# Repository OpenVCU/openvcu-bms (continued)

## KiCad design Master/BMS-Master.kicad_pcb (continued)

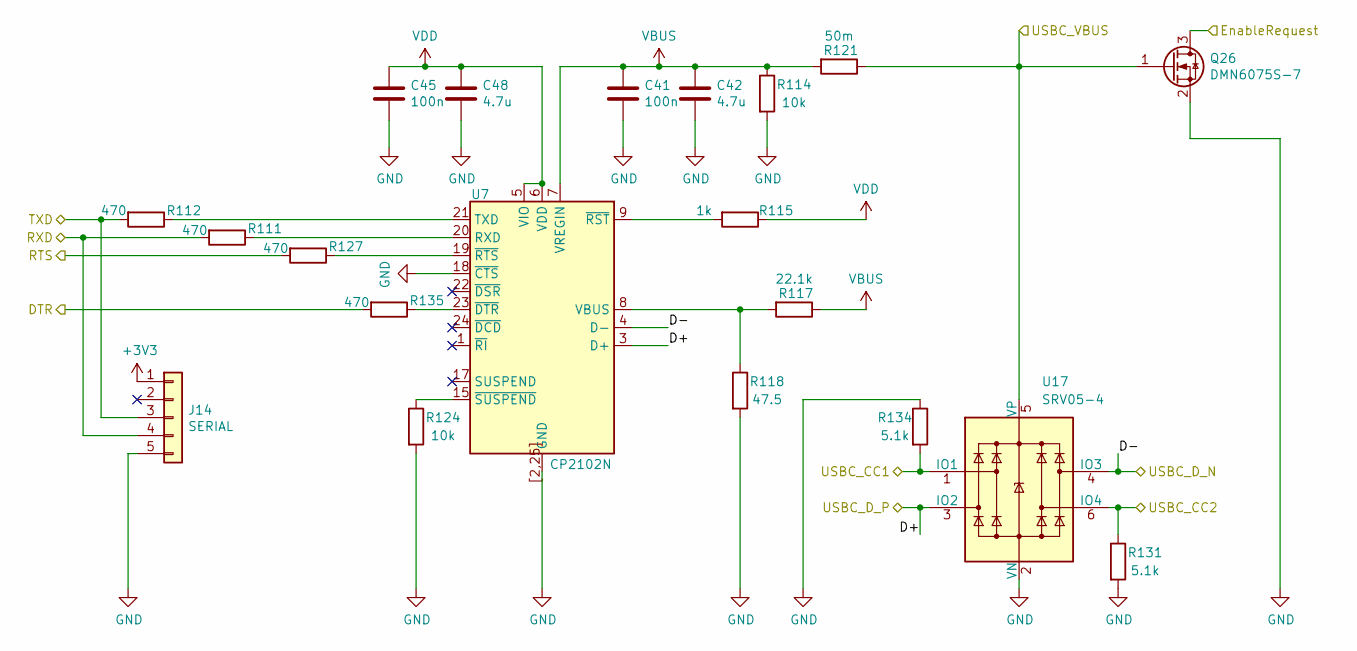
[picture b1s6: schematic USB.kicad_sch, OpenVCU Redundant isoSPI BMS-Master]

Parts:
C41, C45: 100n; C_0603_1608Metric; MPN GRM188R71E104KA01D
C42, C48: 4.7u; C_0805_2012Metric; MPN GRM21BR71E475KA73L
J14: SERIAL; Molex_KK-254_AE-6410-05A_1x05_P2.54mm_Vertical; MPN 70543-0004
Q26: DMN6075S-7; SOT-23; MPN DMN6075S-7
R111, R112, R127, R135: 470; R_0603_1608Metric; MPN RC0603FR-07470RL
R114, R124: 10k; R_0603_1608Metric; MPN RC0603FR-0710KL
R115: 1k; R_0603_1608Metric; MPN MCR03EZPFX1001
R117: 22.1k; R_0603_1608Metric; MPN RC0603FR-0720KL
R118: 47.5; R_0603_1608Metric; MPN RC0603FR-0739KL
R121: 50m; R_1210_3225Metric; MPN RL1210FR-070R05L
R131, R134: 5.1k; R_0603_1608Metric; MPN RC0603FR-075K1L
U7: CP2102N; WQFN-24-1EP_4x4mm_P0.5mm_EP2.45x2.45mm; MPN CP2102N-A02-GQFN24
U17: SRV05-4; SOT-23-6; MPN SRV05-4HTG

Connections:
+3V3: J14.1; also elsewhere on the board
/CAN/EnableRequest: Q26.3 (D); also elsewhere on the board
/LTC6820 STM32/USB_DTR: R135.2; also elsewhere on the board
/LTC6820 STM32/USB_RTS: R127.2; also elsewhere on the board
/LTC6820 STM32/USB_RX: J14.3, R112.2; also elsewhere on the board
/LTC6820 STM32/USB_TX: J14.4, R111.2; also elsewhere on the board
/USB/D+: U7.3 (D+), U17.3 (IO2); also elsewhere on the board
/USB/D-: U7.4 (D-), U17.4 (IO3); also elsewhere on the board
/USB/USBC_CC1: R134.2, U17.1 (IO1); also elsewhere on the board
/USB/USBC_CC2: R131.1, U17.6 (IO4); also elsewhere on the board
/USB/USBC_VBUS: Q26.1 (G), R121.1, U17.5 (VP); also elsewhere on the board
GND: C41.2, C42.2, C45.2, C48.2, J14.5, Q26.2 (S), R114.2, R118.2, R124.2, R131.2, R134.1, U7.2 (GND), U7.18 (~CTS), U7.25 (GND), U7.[2,25] (GND), U17.2 (VN); also elsewhere on the board
unnamed: R111.1, U7.20 (RXD)
unnamed: R112.1, U7.21 (TXD)
unnamed: R117.2, R118.1, U7.8 (VBUS)
unnamed: R135.1, U7.23 (~DTR)
unnamed: R115.2, U7.9 (~RST)
unnamed: R127.1, U7.19 (~RTS)
unnamed: R124.1, U7.15 (~SUSPEND)
VBUS: C41.1, C42.1, R114.1, R117.1, R121.2, U7.7 (VREGIN)
VDD: C45.1, C48.1, R115.1, U7.5 (VIO), U7.6 (VDD)

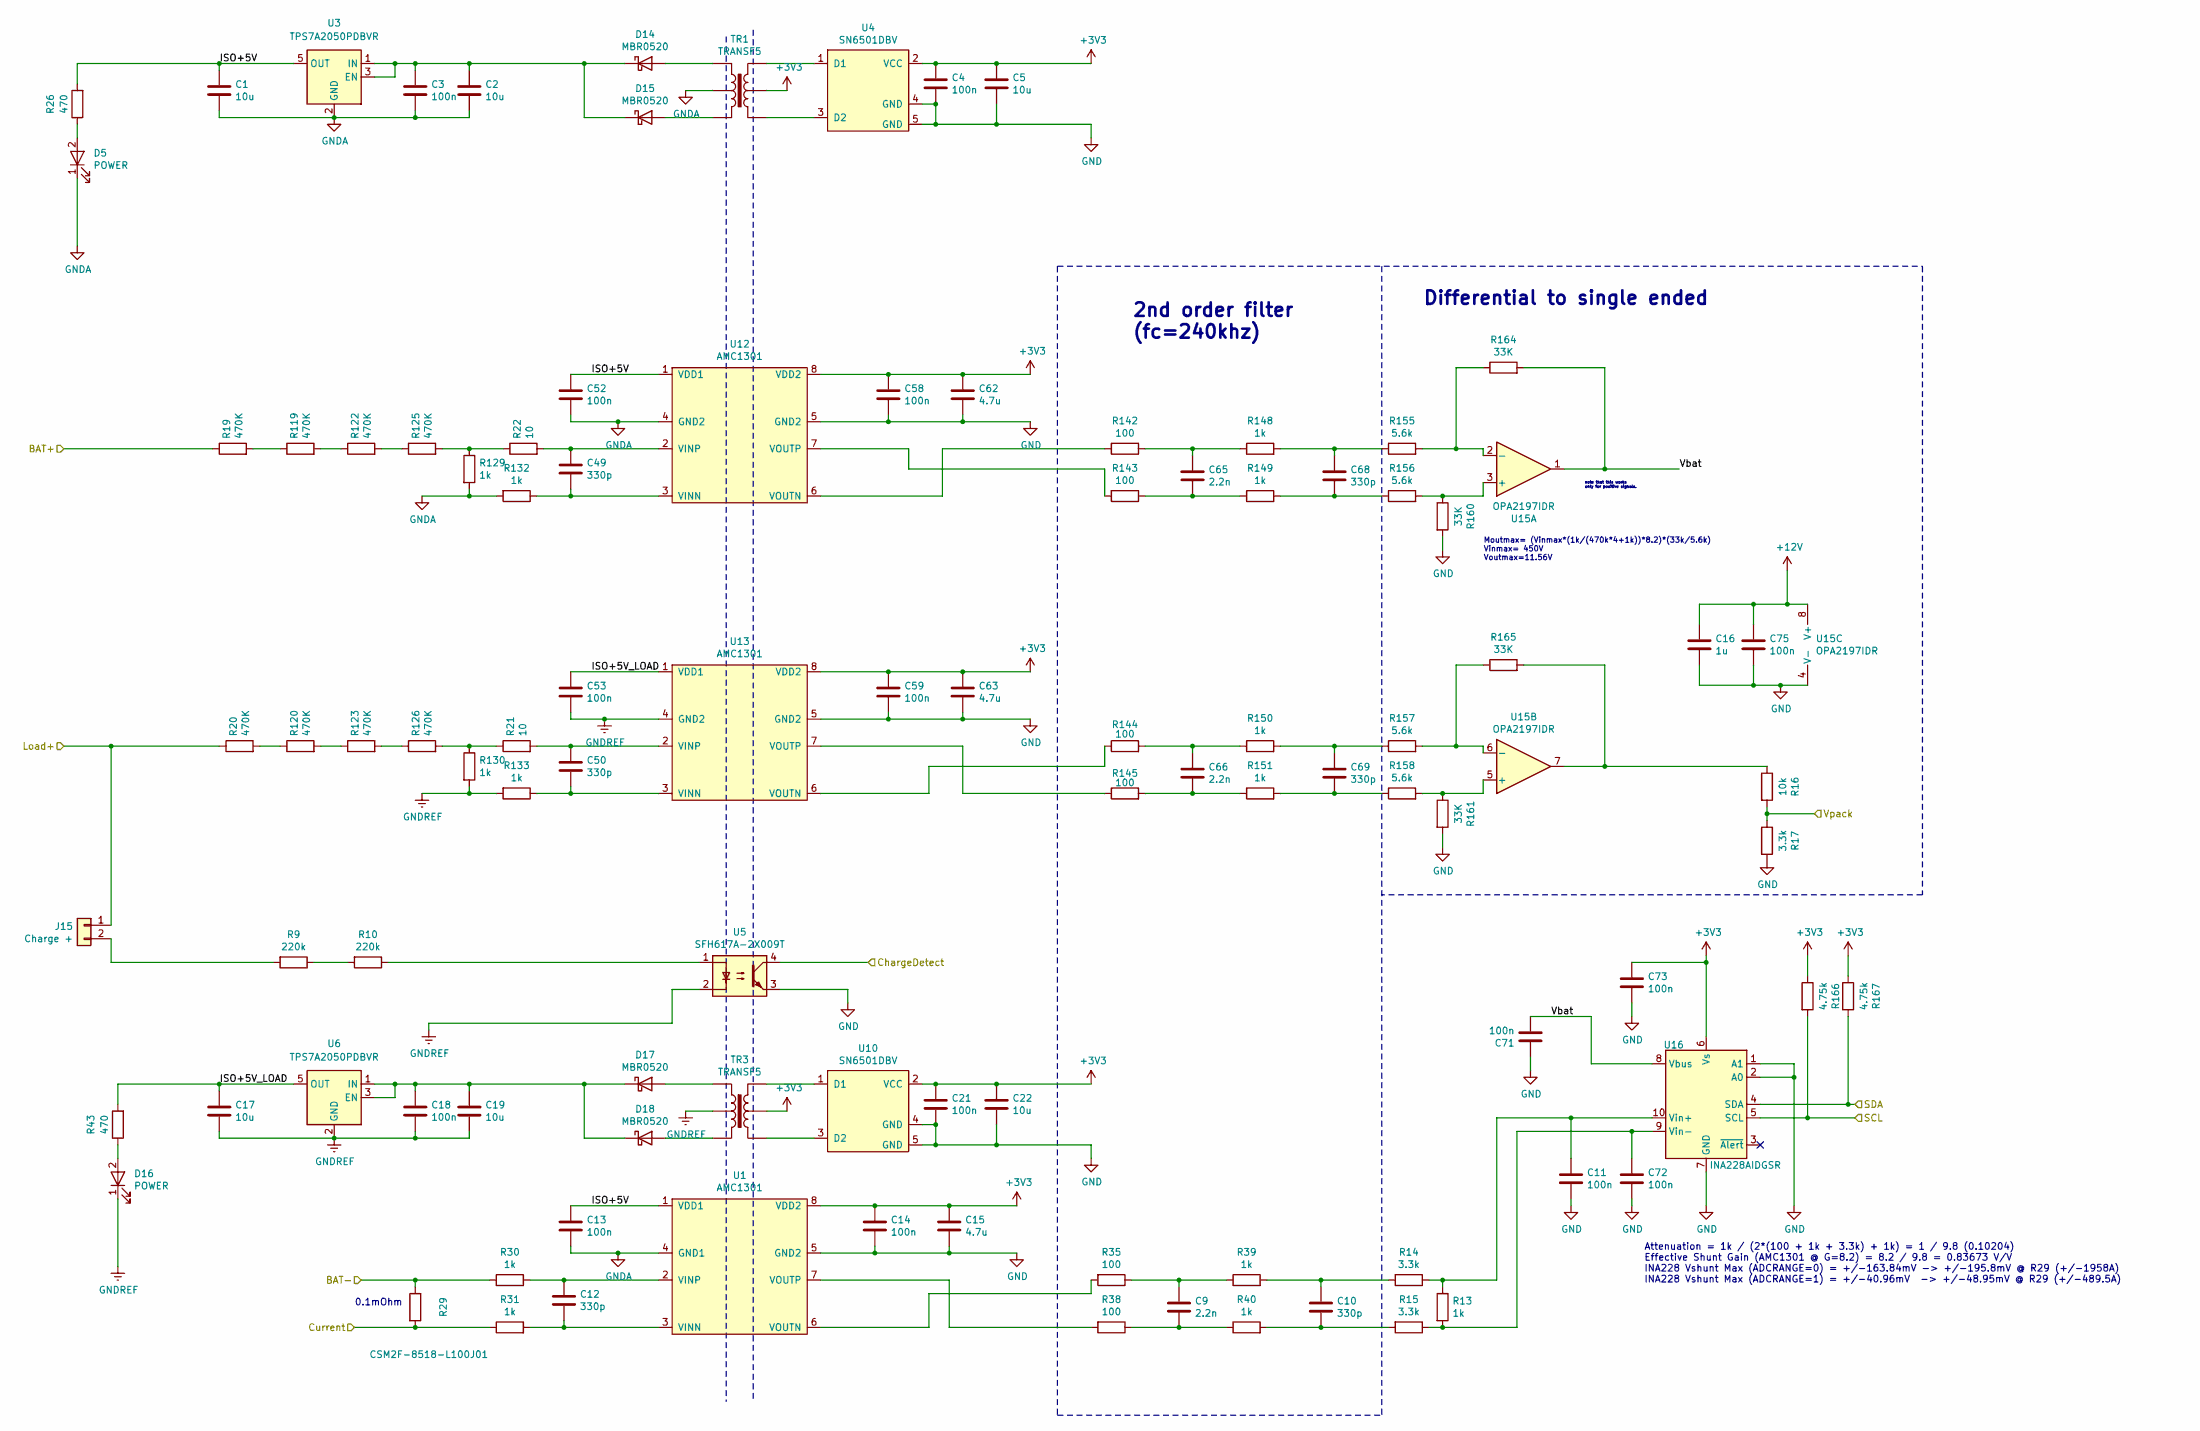
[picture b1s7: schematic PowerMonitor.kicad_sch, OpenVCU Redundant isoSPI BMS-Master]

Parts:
C1, C2, C5, C17, C19, C22: 10u; C_0805_2012Metric; MPN CL21A106KAYNNNE
C3, C4, C11, C13, C14, C18, C21, C52, C53, C58, C59, C71, C72, C73, C75: 100n; C_0603_1608Metric; MPN GRM188R71E104KA01D
C9, C65, C66: 2.2n; C_0603_1608Metric; MPN GRM1885C1H222JA01D
C10, C12, C49, C50, C68, C69: 330p; C_0603_1608Metric; MPN CL10B331KB8NNNC
C15, C62, C63: 4.7u; C_0805_2012Metric; MPN GRM21BR71E475KA73L
C16: 1u; C_0603_1608Metric; MPN GRM188R71E105KA12D
D5, D16: POWER; LED_0603_1608Metric; MPN SML-D12P8WT86C
D14, D15, D17, D18: MBR0520; D_SOD-123; MPN MBR0520L
J15: Charge +; PhoenixContact_GMSTBVA_2,5_2-G_1x02_P7.50mm_Vertical; MPN 1766770
R9, R10: 220k; R_2512_6332Metric; MPN 25121WF2203T4E
R13, R30, R31, R39, R40, R129, R130, R132, R133, R148, R149, R150, R151: 1k; R_0603_1608Metric; MPN MCR03EZPFX1001
R14, R15, R17: 3.3k; R_0603_1608Metric; MPN RC0603FR-073K3L
R16: 10k; R_0603_1608Metric; MPN RC0603FR-0710KL
R19, R20, R119, R120, R122, R123, R125, R126: 470K; R_1206_3216Metric; MPN RC1206FR-07470KL
R21, R22: 10; R_0603_1608Metric; MPN RC0603JR-0710RL
R26, R43: 470; R_0603_1608Metric; MPN RC0603FR-07470RL
R29: CSM2F-8518-L100J01; MPN CSM2F-8518-L100J01
R35, R38, R142, R143, R144, R145: 100; R_0603_1608Metric; MPN RC0603FR-07100RL
R155, R156, R157, R158: 5.6k; R_0603_1608Metric; MPN RC0603FR-075K6L
R160, R161, R164, R165: 33K; R_0603_1608Metric; MPN RC0603FR-0733KL
R166, R167: 4.75k; R_0603_1608Metric; MPN RC0603FR-074K75L
TR1, TR3: TRANSF5; WURTH-760390015; MPN 760390015
U1, U12, U13: AMC1301; SSO-8_6.8x5.9mm_P1.27mm_Clearance8mm; MPN AMC1301DWVR
U3, U6: TPS7A2050PDBVR; SOT-23-5; MPN TPS7A2050PDBVR
U4, U10: SN6501DBV; SOT-23-5; MPN SN6501DBVR
U5: SFH617A-2X009T; SMDIP-4_W9.53mm_Clearance8mm; MPN SFH617A-2X009T
U15: OPA2197IDR; SOIC-8_3.9x4.9mm_P1.27mm; MPN OPA2197IDR
U16: INA228AIDGSR; MSOP-10_3x3mm_P0.5mm; MPN INA228AIDGSR

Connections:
+3V3: C4.1, C5.1, C14.1, C15.1, C21.1, C22.1, C58.1, C59.1, C62.1, C63.1, C73.2, R166.1, R167.1, TR1.5, TR3.5, U1.8 (VDD2), U4.2 (VCC), U10.2 (VCC), U12.8 (VDD2), U13.8 (VDD2), U16.6 (Vs); also elsewhere on the board
+12V: C16.1, C75.1, U15.8 (V+); also elsewhere on the board
/BAT+: R19.1; also elsewhere on the board
/LTC6820 STM32/SCL: R166.2, U16.5 (SCL); also elsewhere on the board
/LTC6820 STM32/SDA: R167.2, U16.4 (SDA); also elsewhere on the board
/LTC6820 STM32/Vpack: R16.2, R17.1; also elsewhere on the board
/Load+: J15.1, R20.1; also elsewhere on the board
/PowerMonitor/Current: R29.2, R31.1; also elsewhere on the board
/PowerMonitor/ISO+5V: C1.1, C13.1, C52.1, R26.2, U1.1 (VDD1), U3.5 (OUT), U12.1 (VDD1)
/PowerMonitor/ISO+5V_LOAD: C17.1, C53.1, R43.2, U6.5 (OUT), U13.1 (VDD1)
/PowerMonitor/Vbat: C71.1, R164.2, U15.1, U16.8 (Vbus)
/PowerSupply/ChargeDetect: U5.4; also elsewhere on the board
GND: C4.2, C5.2, C11.1, C14.2, C15.2, C16.2, C21.2, C22.2, C58.2, C59.2, C62.2, C63.2, C71.2, C72.1, C73.1, C75.2, R17.2, R160.2, R161.2, U1.5 (GND2), U4.4 (GND), U4.5 (GND), U5.3, U10.4 (GND), U10.5 (GND), U12.5 (GND2), U13.5 (GND2), U15.4 (V-), U16.1 (A1), U16.2 (A0), U16.7 (GND); also elsewhere on the board
GNDA: C1.2, C2.2, C3.2, C13.2, C52.2, D5.1 (K), R29.1, R30.1, R129.2, R132.2, TR1.2, U1.4 (GND1), U3.2 (GND), U12.4 (GND2); also elsewhere on the board
GNDREF: C17.2, C18.2, C19.2, C53.2, D16.1 (K), R130.2, R133.2, TR3.2, U5.2, U6.2 (GND), U13.4 (GND2); also elsewhere on the board
unnamed: C9.1, R35.1, R39.1
unnamed: C9.2, R38.1, R40.1
unnamed: C10.1, R14.2, R39.2
unnamed: C10.2, R15.2, R40.2
unnamed: C65.1, R142.1, R148.1
unnamed: C65.2, R143.1, R149.1
unnamed: C66.1, R144.2, R150.1
unnamed: C66.2, R145.2, R151.1
unnamed: C68.1, R148.2, R155.1
unnamed: C68.2, R149.2, R156.1
unnamed: C69.1, R150.2, R157.1
unnamed: C69.2, R151.2, R158.1
unnamed: D5.2 (A), R26.1
unnamed: D14.2 (A), TR1.1
unnamed: C2.1, C3.1, D14.1 (K), D15.1 (K), U3.1 (IN), U3.3 (EN)
unnamed: D15.2 (A), TR1.3
unnamed: D16.2 (A), R43.1
unnamed: D17.2 (A), TR3.1
unnamed: C18.1, C19.1, D17.1 (K), D18.1 (K), U6.1 (IN), U6.3 (EN)
unnamed: D18.2 (A), TR3.3
unnamed: J15.2, R9.2
unnamed: R10.1, U5.1
unnamed: R9.1, R10.2
unnamed: R16.1, R165.2, U15.7
unnamed: R19.2, R119.1
unnamed: R119.2, R122.1
unnamed: R20.2, R120.1
unnamed: R120.2, R123.1
unnamed: R122.2, R125.1
unnamed: R123.2, R126.1
unnamed: R22.1, R125.2, R129.1
unnamed: R21.1, R126.2, R130.1
unnamed: C12.2, R31.2, U1.3 (VINN)
unnamed: C12.1, R30.2, U1.2 (VINP)
unnamed: R35.2, U1.6 (VOUTN)
unnamed: R38.2, U1.7 (VOUTP)
unnamed: TR1.6, U4.1 (D1)
unnamed: TR1.4, U4.3 (D2)
unnamed: TR3.6, U10.1 (D1)
unnamed: TR3.4, U10.3 (D2)
unnamed: C49.2, R132.1, U12.3 (VINN)
unnamed: C49.1, R22.2, U12.2 (VINP)
unnamed: R142.2, U12.6 (VOUTN)
unnamed: R143.2, U12.7 (VOUTP)
unnamed: C50.2, R133.1, U13.3 (VINN)
unnamed: C50.1, R21.2, U13.2 (VINP)
unnamed: R144.1, U13.6 (VOUTN)
unnamed: R145.1, U13.7 (VOUTP)
unnamed: R156.2, R160.1, U15.3 (+)
unnamed: R155.2, R164.1, U15.2 (-)
unnamed: R158.2, R161.1, U15.5 (+)
unnamed: R157.2, R165.1, U15.6 (-)
unnamed: C11.2, R13.1, R14.1, U16.10 (Vin+)
unnamed: C72.2, R13.2, R15.1, U16.9 (Vin-)

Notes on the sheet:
Moutmax= (Vinmax*(1k/(470k*4+1k))*8.2)*(33k/5.6k) Vinmax= 450V Voutmax=11.56V
0.1mOhm
note that this works only for positive signals.
Differential to single ended
Attenuation = 1k / (2*(100 + 1k + 3.3k) + 1k) = 1 / 9.8 (0.10204) Effective Shunt Gain (AMC1301 @ G=8.2) = 8.2 / 9.8 = 0.83673 V/V INA228 Vshunt Max (ADCRANGE=0) = +/-163.84mV -> +/-195.8mV @ R29 (+/-1958A) INA228 Vshunt Max (ADCRANGE=1) = +/-40.96mV -> +/-48.95mV @ R29 (+/-489.5A)
2nd order filter (fc=240khz)

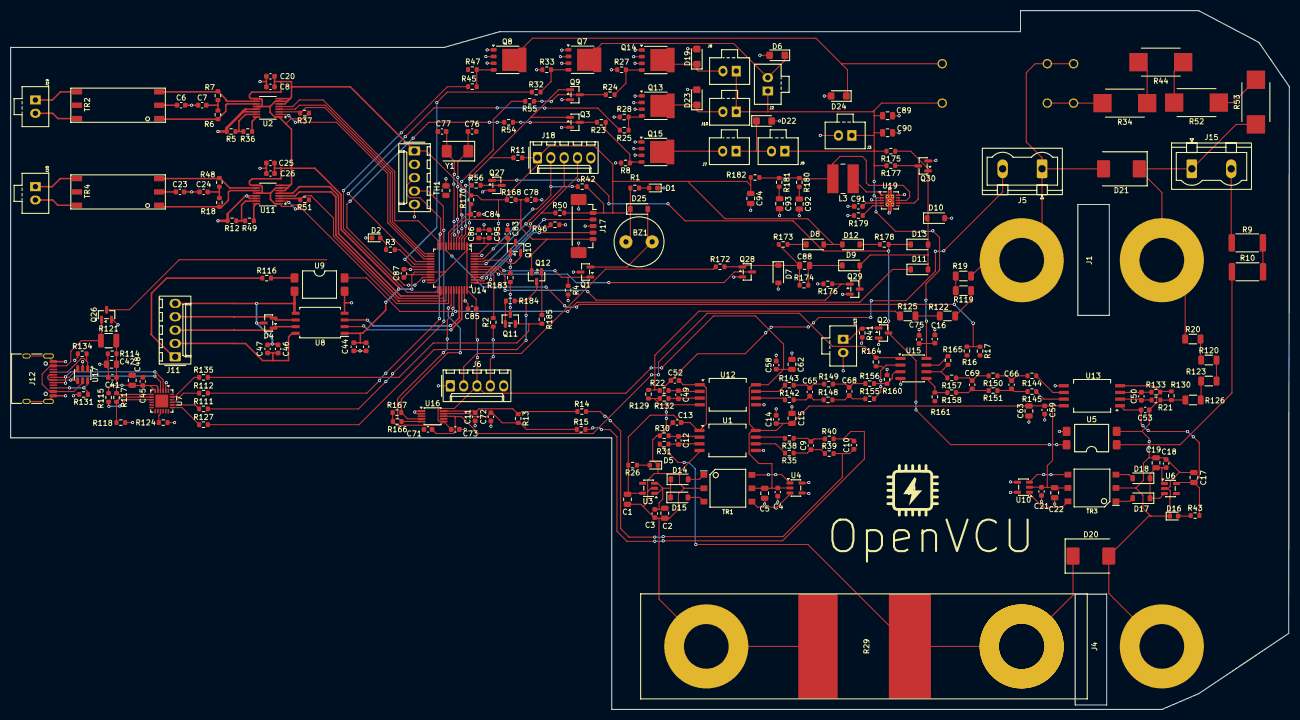
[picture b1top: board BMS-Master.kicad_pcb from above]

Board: 2 copper layers, 243.4 x 133.0 mm, 267 parts (1 on the bottom side), 182 nets.

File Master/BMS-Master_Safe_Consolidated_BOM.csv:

Reference,Qty,Value,MPN,DNP,Exclude from BOM,Exclude from Board,Footprint,Datasheet,Sheets
"C10,C12,C49,C50,C68,C69",6,330p,CL10B331KB8NNNC,,,,Capacitor_SMD:C_0603_1608Metric,~,PowerMonitor
C91,1,47n,GCM188R71H473KA55D,,,,Capacitor_SMD:C_0603_1608Metric,~,PowerSupply
"C9,C65,C66",3,2.2n,GRM1885C1H222JA01D,,,,Capacitor_SMD:C_0603_1608Metric,~,PowerMonitor
"C76,C77",2,27p,GRM1885C1H270JA01D,,,,Capacitor_SMD:C_0603_1608Metric,~,MCU
"C3,C4,C8,C11,C13,C14,C18,C21,C26,C41,C44,C45,C47,C52,C53,C58,C59,C71,C72,C73,C75,C78,C83,C84,C85,C86,C87,C95",28,100n,GRM188R71E104KA01D,,,,Capacitor_SMD:C_0603_1608Metric,~,"CAN, MCU, PowerMonitor, USB"
"C16,C20,C25,C43,C46",5,1u,GRM188R71E105KA12D,,,,Capacitor_SMD:C_0603_1608Metric,~,"CAN, MCU, PowerMonitor"
"C6,C7,C23,C24",4,10n,GRM188R71H103KA01D,,,,Capacitor_SMD:C_0603_1608Metric,~,MCU
"C1,C2,C5,C17,C19,C22,C92,C93,C94",9,10u,CL21A106KAYNNNE,,,,Capacitor_SMD:C_0805_2012Metric,~,"PowerMonitor, PowerSupply"
"C89,C90",2,22u,CL21A226MAQNNNE,,,,Capacitor_SMD:C_0805_2012Metric,~,PowerSupply
"C15,C42,C48,C62,C63,C88",6,4.7u,GRM21BR71E475KA73L,,,,Capacitor_SMD:C_0805_2012Metric,~,"PowerMonitor, PowerSupply, USB"
"J6,J11,J14,J18",4,CAN / OLED / Power Button / SERIAL,70543-0004,,,,Connector_Molex:Molex_KK-254_AE-6410-05A_1x05_P2.54mm_Vertical,~,"BMS-Master, USB"
J17,1,DEBUG,53398-0571,,,,Connector_Molex:Molex_PicoBlade_53398-0571_1x05-1MP_P1.25mm_Vertical,~,MCU
"J5,J15",2,Charge + / Power,1766770,,,,"Connector_Phoenix_GMSTB:PhoenixContact_GMSTBVA_2,5_2-G_1x02_P7.50mm_Vertical",~,"BMS-Master, PowerMonitor"
J12,1,USB_C_Receptacle_USB2.0_16P,TYPE-C-31-M-12,,,,Connector_USB:USB_C_Receptacle_HRO_TYPE-C-31-M-12,https://www.usb.org/sites/default/files/documents/usb_type-c.zip,BMS-Master
Y1,1,8MHz,ABM3-8.000MHZ-D2Y-T,,,,Crystal:Crystal_SMD_Abracon_ABM3-2Pin_5.0x3.2mm,~,MCU
"D20,D21",2,SMCJ440CA,SMCJ440CA,,,,Diode_SMD:D_SMC,~,BMS-Master
"D6,D19,D22,D23,D24",5,SMF24A,SMF24A,,,,Diode_SMD:D_SMF,https://www.vishay.com/doc?85881,BMS-Master
"D8,D9,D11,D12,D13,D25",6,1N4148W,1N4148W-7-F,,,,Diode_SMD:D_SOD-123,https://www.vishay.com/docs/85748/1n4148w.pdf,"BMS-Master, PowerSupply"
"D7,D10",2,BZT52C16,BZT52C16-E3-08,,,,Diode_SMD:D_SOD-123,https://diotec.com/tl_files/diotec/files/pdf/datasheets/bzt5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,PowerSupply
"D14,D15,D17,D18",4,MBR0520,MBR0520L,,,,Diode_SMD:D_SOD-123,http://www.mccsemi.com/up_pdf/MBR0520~MBR0580(SOD123).pdf,PowerMonitor
L3,1,744043151,744043151,,,,Inductor_SMD:L_Wuerth_WE-PD2-Typ-MS,~,PowerSupply
"D1,D2,D5,D16",4,POWER / STATUS,SML-D12P8WT86C,,,,LED_SMD:LED_0603_1608Metric,~,"BMS-Master, PowerMonitor"
BZ1,1,AI-1027-TWT-5V,AI-1027-TWT-5V-2-R,,,,OpenVCU:BUZZER,~,BMS-Master
R29,1,CSM2F-8518-L100J01,CSM2F-8518-L100J01,,,,OpenVCU:CSM2F-8518-L100J01,~,PowerMonitor
"TR2,TR4",2,HM2108NL,HM2108NL,,,,OpenVCU:HM2108NL,,MCU
"J2,J3,J7,J8,J9,J10,J13,J19,J20",9,+ 12V - / Charge / Charger / Cooling / Discharge / E-Stop / ISOSPI1 / ISOSPI2,70543-0001,,,,OpenVCU:Pin_1x02-XL,~,"BMS-Master, PowerSupply"
K1,1,SHV12-1A85-78L3K,SHV12-1A85-78L3K,,,,OpenVCU:SHV12-1AB5-7BL3K,,BMS-Master
"R34,R44,R52,R53",4,135,SMW3135RJT,,,,OpenVCU:SM_3,~,BMS-Master
U8,1,ISO1042QDWVRQ1,ISO1042QDWVRQ1,,,,OpenVCU:SOIC-8W_7.5x5.85mm_Pitch1.27mm,https://www.ti.com/lit/ds/symlink/iso1042-q1.pdf,CAN
"TR1,TR3",2,TRANSF5,760390014,,,,OpenVCU:WURTH-760390014,,PowerMonitor
U7,1,CP2102C-Axx-xQFN24,CP2102C-A01-GQFN24,,,,Package_DFN_QFN:WQFN-24-1EP_4x4mm_P0.5mm_EP2.45x2.45mm,https://www.silabs.com/documents/public/data-sheets/cp2102c-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,USB
"U5,U9",2,SFH617A-2X009T,SFH617A-2X009T,,,,Package_DIP:SMDIP-4_W9.53mm_Clearance8mm,http://www.vishay.com/docs/83740/sfh617a.pdf,"CAN, PowerMonitor"
U14,1,STM32G474CCTx,STM32G474CCT6,,,,Package_QFP:LQFP-48_7x7mm_P0.5mm,https://www.st.com/resource/en/datasheet/stm32g474cc.pdf,MCU
U16,1,INA228AIDGSR,INA228AIDGSR,,,,Package_SO:MSOP-10_3x3mm_P0.5mm,https://www.ti.com/lit/ds/symlink/ina228.pdf,PowerMonitor
"U2,U11",2,LTC6820,LTC6820IMS#PBF,,,,Package_SO:MSOP-16_3x4.039mm_P0.5mm,https://www.analog.com/media/en/technical-documentation/data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,MCU
U15,1,OPA2197IDR,OPA2197IDR,,,,Package_SO:SOIC-8_3.9x4.9mm_P1.27mm,https://www.ti.com/lit/ds/symlink/opa2197.pdf,PowerMonitor
"U1,U12,U13",3,AMC1301,AMC1301DWVR,,,,Package_SO:SSO-8_6.8x5.9mm_P1.27mm_Clearance8mm,https://www.ti.com/lit/ds/symlink/amc1301.pdf,PowerMonitor
U19,1,LM5165YDRC,LM5165YDRCR,,,,Package_SON:Texas_S-PVSON-N10_ThermalVias,http://www.ti.com/lit/ds/symlink/lm5165.pdf,PowerSupply
"Q7,Q8,Q13,Q14,Q15",5,"BUK9Y40-55B,115","BUK9Y40-55B,115",,,,Package_TO_SOT_SMD:LFPAK56,https://assets.nexperia.com/documents/data-sheet/BUK9Y40-55B.pdf,Interfaces
"Q1,Q2,Q3,Q9,Q26,Q27,Q28,Q29,Q30",9,DMN6075S-7,DMN6075S-7,,,,Package_TO_SOT_SMD:SOT-23,https://www.diodes.com/assets/Datasheets/DMN6075S.pdf,"BMS-Master, Interfaces, MCU, PowerSupply, USB"
"Q10,Q11",2,MMBT3904,MMBT3904LT1G,,,,Package_TO_SOT_SMD:SOT-23,https://www.onsemi.com/pdf/datasheet/pzt3904-d.pdf,MCU
Q12,1,MMBT3906,MMBT3906LT1G,,,,Package_TO_SOT_SMD:SOT-23,https://www.onsemi.com/pdf/datasheet/pzt3906-d.pdf,MCU
D4,1,SZNUP2105L,SZNUP2105LT1G,,,,Package_TO_SOT_SMD:SOT-23,http://www.onsemi.com/pub_link/Collateral/NUP2105L-D.PDF,CAN
"U4,U10",2,SN6501DBV,SN6501DBVR,,,,Package_TO_SOT_SMD:SOT-23-5,https://www.ti.com/lit/ds/symlink/sn6501.pdf,PowerMonitor
"U3,U6",2,TPS7A2050PDBVR,TPS7A2050PDBVR,,,,Package_TO_SOT_SMD:SOT-23-5,https://www.ti.com/lit/ds/symlink/tps7a20.pdf,PowerMonitor
U17,1,SRV05-4,SRV05-4HTG,,,,Package_TO_SOT_SMD:SOT-23-6,http://www.onsemi.com/pub/Collateral/SRV05-4-D.PDF,USB
"R13,R30,R31,R39,R40,R54,R55,R56,R115,R129,R130,R132,R133,R148,R149,R150,R151",17,1k,MCR03EZPFX1001,,,,Resistor_SMD:R_0603_1608Metric,~,"Interfaces, MCU, PowerMonitor, USB"
"R35,R38,R142,R143,R144,R145,R172",7,100,RC0603FR-07100RL,,,,Resistor_SMD:R_0603_1608Metric,~,"PowerMonitor, PowerSupply"
"R4,R8,R11,R16,R27,R28,R33,R41,R47,R114,R124,R168,R170,R173,R176,R178,R183,R184,R185",19,10k,RC0603FR-0710KL,,,,Resistor_SMD:R_0603_1608Metric,~,"BMS-Master, Interfaces, MCU, PowerMonitor, PowerSupply, USB"
R179,1,130k,RC0603FR-07130KL,,,,Resistor_SMD:R_0603_1608Metric,~,PowerSupply
"R5,R12",2,1.2k,RC0603FR-071K2L,,,,Resistor_SMD:R_0603_1608Metric,~,MCU
"R180,R181,R182",3,1,RC0603FR-071RL,,,,Resistor_SMD:R_0603_1608Metric,~,PowerSupply
R117,1,20k,RC0603FR-0720KL,,,,Resistor_SMD:R_0603_1608Metric,~,USB
"R37,R51",2,2k,RC0603FR-072KL,,,,Resistor_SMD:R_0603_1608Metric,~,MCU
"R160,R161,R164,R165",4,33K,RC0603FR-0733KL,,,,Resistor_SMD:R_0603_1608Metric,~,PowerMonitor
R118,1,39k,RC0603FR-0739KL,,,,Resistor_SMD:R_0603_1608Metric,~,USB
"R14,R15,R17",3,3.3k,RC0603FR-073K3L,,,,Resistor_SMD:R_0603_1608Metric,~,PowerMonitor
"R1,R2,R3,R26,R43,R111,R112,R127,R135",9,470,RC0603FR-07470RL,,,,Resistor_SMD:R_0603_1608Metric,~,"BMS-Master, PowerMonitor, USB"
"R42,R46,R50,R166,R167",5,4.75k,RC0603FR-074K75L,,,,Resistor_SMD:R_0603_1608Metric,~,"BMS-Master, PowerMonitor"
"R175,R177",2,4.7M,RC0603FR-074M7L,,,,Resistor_SMD:R_0603_1608Metric,~,PowerSupply
"R131,R134",2,5.1k,RC0603FR-075K1L,,,,Resistor_SMD:R_0603_1608Metric,~,USB
"R155,R156,R157,R158",4,5.6k,RC0603FR-075K6L,,,,Resistor_SMD:R_0603_1608Metric,~,PowerMonitor
"R6,R7,R18,R48",4,60.4,RC0603FR-0760R4L,,,,Resistor_SMD:R_0603_1608Metric,~,MCU
"R36,R49",2,806,RC0603FR-07806RL,,,,Resistor_SMD:R_0603_1608Metric,~,MCU
"R21,R22,R23,R24,R25,R32,R45",7,10,RC0603JR-0710RL,,,,Resistor_SMD:R_0603_1608Metric,~,"Interfaces, PowerMonitor"
R174,1,1M,RC0603JR-071ML,,,,Resistor_SMD:R_0603_1608Metric,~,PowerSupply
R116,1,2.2k,RC0603JR-072K2L,,,,Resistor_SMD:R_0603_1608Metric,~,CAN
TH1,1,Thermistor_NTC 100K,SDNT2012X104F4250FTF,,,,Resistor_SMD:R_0805_2012Metric,~,Interfaces
"R19,R20,R119,R120,R122,R123,R125,R126",8,470K,RC1206FR-07470KL,,,,Resistor_SMD:R_1206_3216Metric,~,PowerMonitor
R121,1,50m,RL1210FR-070R05L,,,,Resistor_SMD:R_1210_3225Metric,~,USB
"R9,R10",2,220k,25121WF2203T4E,,,,Resistor_SMD:R_2512_6332Metric,~,PowerMonitor
